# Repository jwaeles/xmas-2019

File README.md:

# xmas-2019
Dynamic christmas gift label that scrolls the name of the person it's for when you shake the gift

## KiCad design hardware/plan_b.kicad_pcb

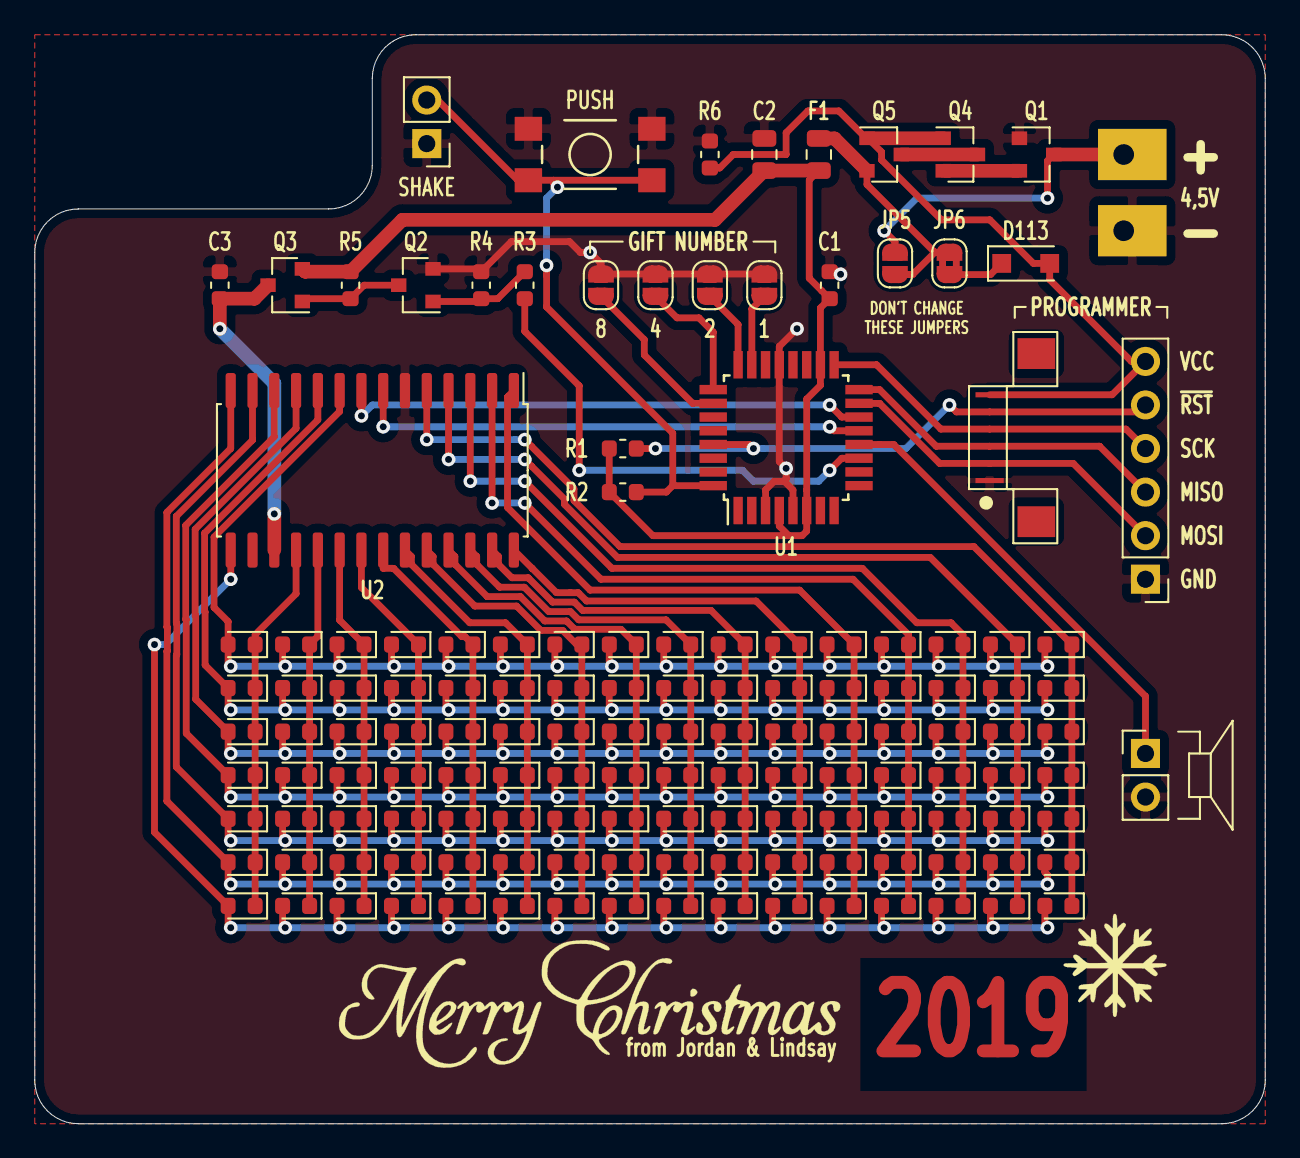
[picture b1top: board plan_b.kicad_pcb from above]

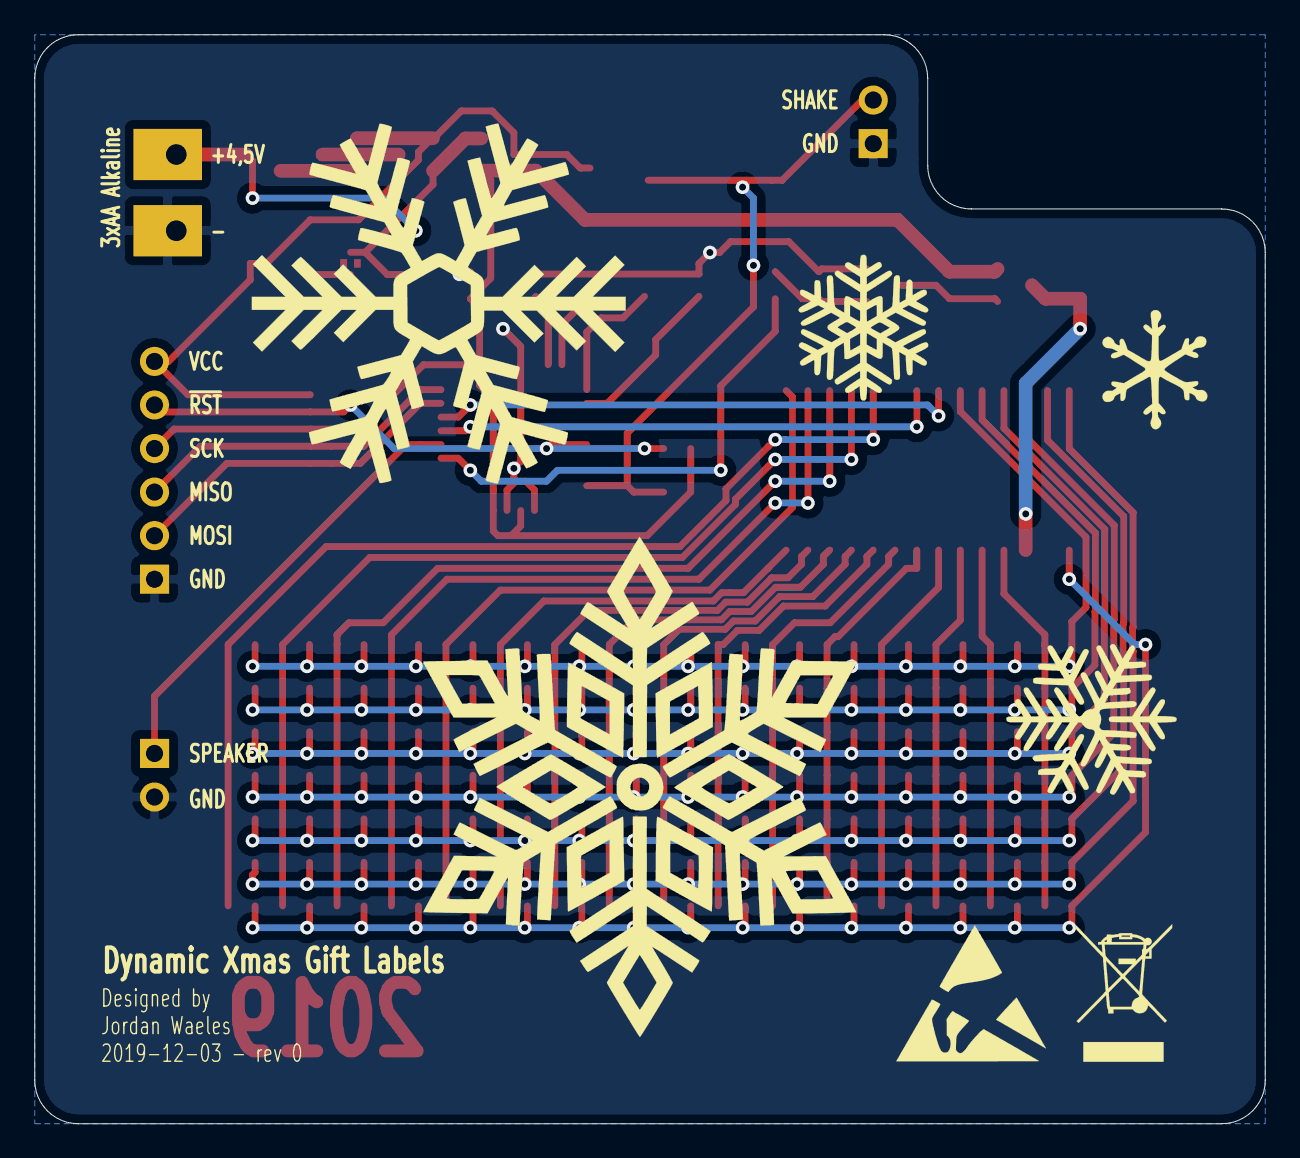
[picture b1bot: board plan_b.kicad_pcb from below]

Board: 2 copper layers, 71.8 x 63.5 mm, 150 parts (5 on the bottom side), 47 nets.

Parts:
C1, C3: 100nF; C_0603_1608Metric
C2: 10uF; C_0805_2012Metric
D1, D2, D3, D4, D5, D6, D7, D8, D9, D10, D11, D12, D13, D14, D15, D16, D17, D18, D19, D20, D21, D22, D23, D24, D25, D26, D27, D28, D29, D30, D31, D32, D33, D34, D35, D36, D37, D38, D39, D40, D41, D42, D43, D44, D45, D46, D47, D48, D49, D50, D51, D52, D53, D54, D55, D56, D57, D58, D59, D60, D61, D62, D63, D64, D65, D66, D67, D68, D69, D70, D71, D72, D73, D74, D75, D76, D77, D78, D79, D80, D81, D82, D83, D84, D85, D86, D87, D88, D89, D90, D91, D92, D93, D94, D95, D96, D97, D98, D99, D100, D101, D102, D103, D104, D105, D106, D107, D108, D109, D110, D111, D112: WHITE; LED_0603_1608Metric
D113: SM4007PL; D_SOD-123F
F1: 500mA; Fuse_0805_2012Metric
J1: +4,5V; LARGE_PAD
J2: -; LARGE_PAD
J3: PROG; FPC_6_1MM_C262383
J4: PROG; PinHeader_1x06_P2.54mm_Vertical
JP1: 1; SolderJumper-2_P1.3mm_Open_RoundedPad1.0x1.5mm
JP2: 2; SolderJumper-2_P1.3mm_Open_RoundedPad1.0x1.5mm
JP3: 4; SolderJumper-2_P1.3mm_Open_RoundedPad1.0x1.5mm
JP4: 8; SolderJumper-2_P1.3mm_Open_RoundedPad1.0x1.5mm
JP5: BYPASS PROTECTION; SolderJumper-2_P1.3mm_Open_RoundedPad1.0x1.5mm
JP6: PROG VCC; SolderJumper-2_P1.3mm_Bridged2Bar_RoundedPad1.0x1.5mm
LS1: 8 ohm; PinHeader_1x02_P2.54mm_Vertical
Q1, Q3, Q4, Q5: Si2301CDS; SOT-23
Q2: S8050; SOT-23
R1, R5: 10K; R_0603_1608Metric
R2, R4, R6: 100K; R_0603_1608Metric
R3: 1K; R_0603_1608Metric
Ref**: Val**; flake-9-30mm
Ref**#2: Val**; flake-2-10mm
Ref**#3: Val**; flake-40-8mm
Ref**#4: Val**; flake-3-10mm
Ref**#5: Val**; flake-11-22mm
Ref**#6: Val**; flake-48-7mm
Ref**#7: Val**; merry-xmas
SW1: SHAKE; PinHeader_1x02_P2.54mm_Vertical
SW2: PUSH; TL3305_TACT_SWITCH_OK
U1: ATmega328P-AU; TQFP-32_7x7mm_P0.8mm
U2: TM1640; SOIC-28W_7.5x17.9mm_P1.27mm

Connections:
/GIFTNR_1: JP1.1, U1.23
/GIFTNR_2: JP2.1, U1.24
/GIFTNR_4: JP3.1, U1.25
/GIFTNR_8: JP4.1, U1.26
/MATRIX_CLK: U1.14, U2.8
/MATRIX_DATA: U1.13, U2.7
/MATRIX_ENABLE: R3.2, U1.11
/MISO: J3.3, J4.3, U1.16
/MOSI: J3.2, J4.2, U1.15
/PROG_VCC: D113.2, J3.6, J4.6, Q4.1, Q5.1, R6.1
/PowerInput/BATT+: J1.1, JP5.1, Q1.3
/SCK: J3.4, J4.4, U1.17
/SPEAKER: LS1.1, U1.12
/TM1640/GRID1: D1.1, D2.1, D3.1, D4.1, D5.1, D6.1, D7.1, U2.18
/TM1640/GRID2: D8.1, D9.1, D10.1, D11.1, D12.1, D13.1, D14.1, U2.19
/TM1640/GRID3: D15.1, D16.1, D17.1, D18.1, D19.1, D20.1, D21.1, U2.20
/TM1640/GRID4: D22.1, D23.1, D24.1, D25.1, D26.1, D27.1, D28.1, U2.21
/TM1640/GRID5: D29.1, D30.1, D31.1, D32.1, D33.1, D34.1, D35.1, U2.22
/TM1640/GRID6: D36.1, D37.1, D38.1, D39.1, D40.1, D41.1, D42.1, U2.23
/TM1640/GRID7: D43.1, D44.1, D45.1, D46.1, D47.1, D48.1, D49.1, U2.24
/TM1640/GRID8: D50.1, D51.1, D52.1, D53.1, D54.1, D55.1, D56.1, U2.25
/TM1640/GRID9: D57.1, D58.1, D59.1, D60.1, D61.1, D62.1, D63.1, U2.26
/TM1640/GRID10: D64.1, D65.1, D66.1, D67.1, D68.1, D69.1, D70.1, U2.27
/TM1640/GRID11: D71.1, D72.1, D73.1, D74.1, D75.1, D76.1, D77.1, U2.28
/TM1640/GRID12: D78.1, D79.1, D80.1, D81.1, D82.1, D83.1, D84.1, U2.1
/TM1640/GRID13: D85.1, D86.1, D87.1, D88.1, D89.1, D90.1, D91.1, U2.2
/TM1640/GRID14: D92.1, D93.1, D94.1, D95.1, D96.1, D97.1, D98.1, U2.3
/TM1640/GRID15: D99.1, D100.1, D101.1, D102.1, D103.1, D104.1, D105.1, U2.4
/TM1640/GRID16: D106.1, D107.1, D108.1, D109.1, D110.1, D111.1, D112.1, U2.5
/TM1640/SEG1: D1.2, D8.2, D15.2, D22.2, D29.2, D36.2, D43.2, D50.2, D57.2, D64.2, D71.2, D78.2, D85.2, D92.2, D99.2, D106.2, U2.9
/TM1640/SEG2: D2.2, D9.2, D16.2, D23.2, D30.2, D37.2, D44.2, D51.2, D58.2, D65.2, D72.2, D79.2, D86.2, D93.2, D100.2, D107.2, U2.10
/TM1640/SEG3: D3.2, D10.2, D17.2, D24.2, D31.2, D38.2, D45.2, D52.2, D59.2, D66.2, D73.2, D80.2, D87.2, D94.2, D101.2, D108.2, U2.11
/TM1640/SEG4: D4.2, D11.2, D18.2, D25.2, D32.2, D39.2, D46.2, D53.2, D60.2, D67.2, D74.2, D81.2, D88.2, D95.2, D102.2, D109.2, U2.12
/TM1640/SEG5: D5.2, D12.2, D19.2, D26.2, D33.2, D40.2, D47.2, D54.2, D61.2, D68.2, D75.2, D82.2, D89.2, D96.2, D103.2, D110.2, U2.13
/TM1640/SEG6: D6.2, D13.2, D20.2, D27.2, D34.2, D41.2, D48.2, D55.2, D62.2, D69.2, D76.2, D83.2, D90.2, D97.2, D104.2, D111.2, U2.14
/TM1640/SEG7: D7.2, D14.2, D21.2, D28.2, D35.2, D42.2, D49.2, D56.2, D63.2, D70.2, D77.2, D84.2, D91.2, D98.2, D105.2, D112.2, U2.15
/~RST: J3.5, J4.5, R1.2, U1.29
/~SHAKE_INT: R2.2, SW1.2, SW2.1, U1.32
GND: C1.2, C2.2, C3.2, J2.1, J3.1, J4.1, JP1.2, JP2.2, JP3.2, JP4.2, LS1.2, Q1.1, Q2.2, R4.2, R6.2, SW1.1, SW2.2, U1.3, U1.5, U1.21, U2.6
unnamed: C3.1, Q3.3, U2.17
unnamed: D113.1, JP6.2
unnamed: F1.2, JP5.2, JP6.1, Q5.2
unnamed: Q1.2, Q4.2
unnamed: Q2.1, R3.1, R4.1
unnamed: Q2.3, Q3.1, R5.2
unnamed: Q4.3, Q5.3
VCC: C1.1, C2.1, F1.1, Q3.2, R1.1, R2.1, R5.1, U1.4, U1.6, U1.18

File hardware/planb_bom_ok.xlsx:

Comment | Designator | Footprint | LCSC Part #（optional）
100nF | C3,C1 | C_0603_1608Metric | C14663
ATmega328P-AU | U1 | TQFP-32_7x7mm_P0.8mm | C14877
WHITE | D1,D2,D3,D4,D5,D6,D7,D8,D9,D10,D11,D12,D13,D14,D15,D16,D17,D18,D19,D20,D21,D22,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 | LED_0603_1608Metric | C2290
S8050 | Q2 | SOT-23 | C2146
Si2301CDS | Q3,Q1,Q4,Q5 | SOT-23 | C10487
100K | R2,R4,R6 | R_0603_1608Metric | C25803
1K | R3 | R_0603_1608Metric | C21190
10K | R5,R1 | R_0603_1608Metric | C25804
TM1640 | U2 | SOIC-28W_7.5x17.9mm_P1.27mm | C41327
10uF | C2 | C_0805_2012Metric | C15850
SM4007PL | D113 | D_SOD-123F | C64898
500mA | F1 | Fuse_0805_2012Metric | C261942

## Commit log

2019-12-04 Adding PDF of schematic
2019-12-23 Firmware, uploaded as programmed on the gifts
2019-12-23 Added comments on the schematic, updated PDF
